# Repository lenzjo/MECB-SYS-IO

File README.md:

# TLC SYS-IO for MECB

This board consists of the following:

- SCC2691 ACIA

- WDC6522N

- RTC72421 - with battery backup

- ATTINY261A-P -for PS/2 Keyboard

I have brought out all available outputs along the top of the PCB, however, the PS/2 clock and data signals are also on the connector (pins C11 and A12 repectively) as are TxD (A16), RxD (A17), RTS (C16) and CTS (C19).

Use at your own risk as I have not had time yet to fully test the PCB. 

Also, the battery holder is an SMD part. It's easy enough to attach, I used a heat gun from underneath the pcb.

UPDATES

1.3 - Fixed Reset line on SCC2691, updated battery holder.

1.4 - Fixed KYBD clk line.

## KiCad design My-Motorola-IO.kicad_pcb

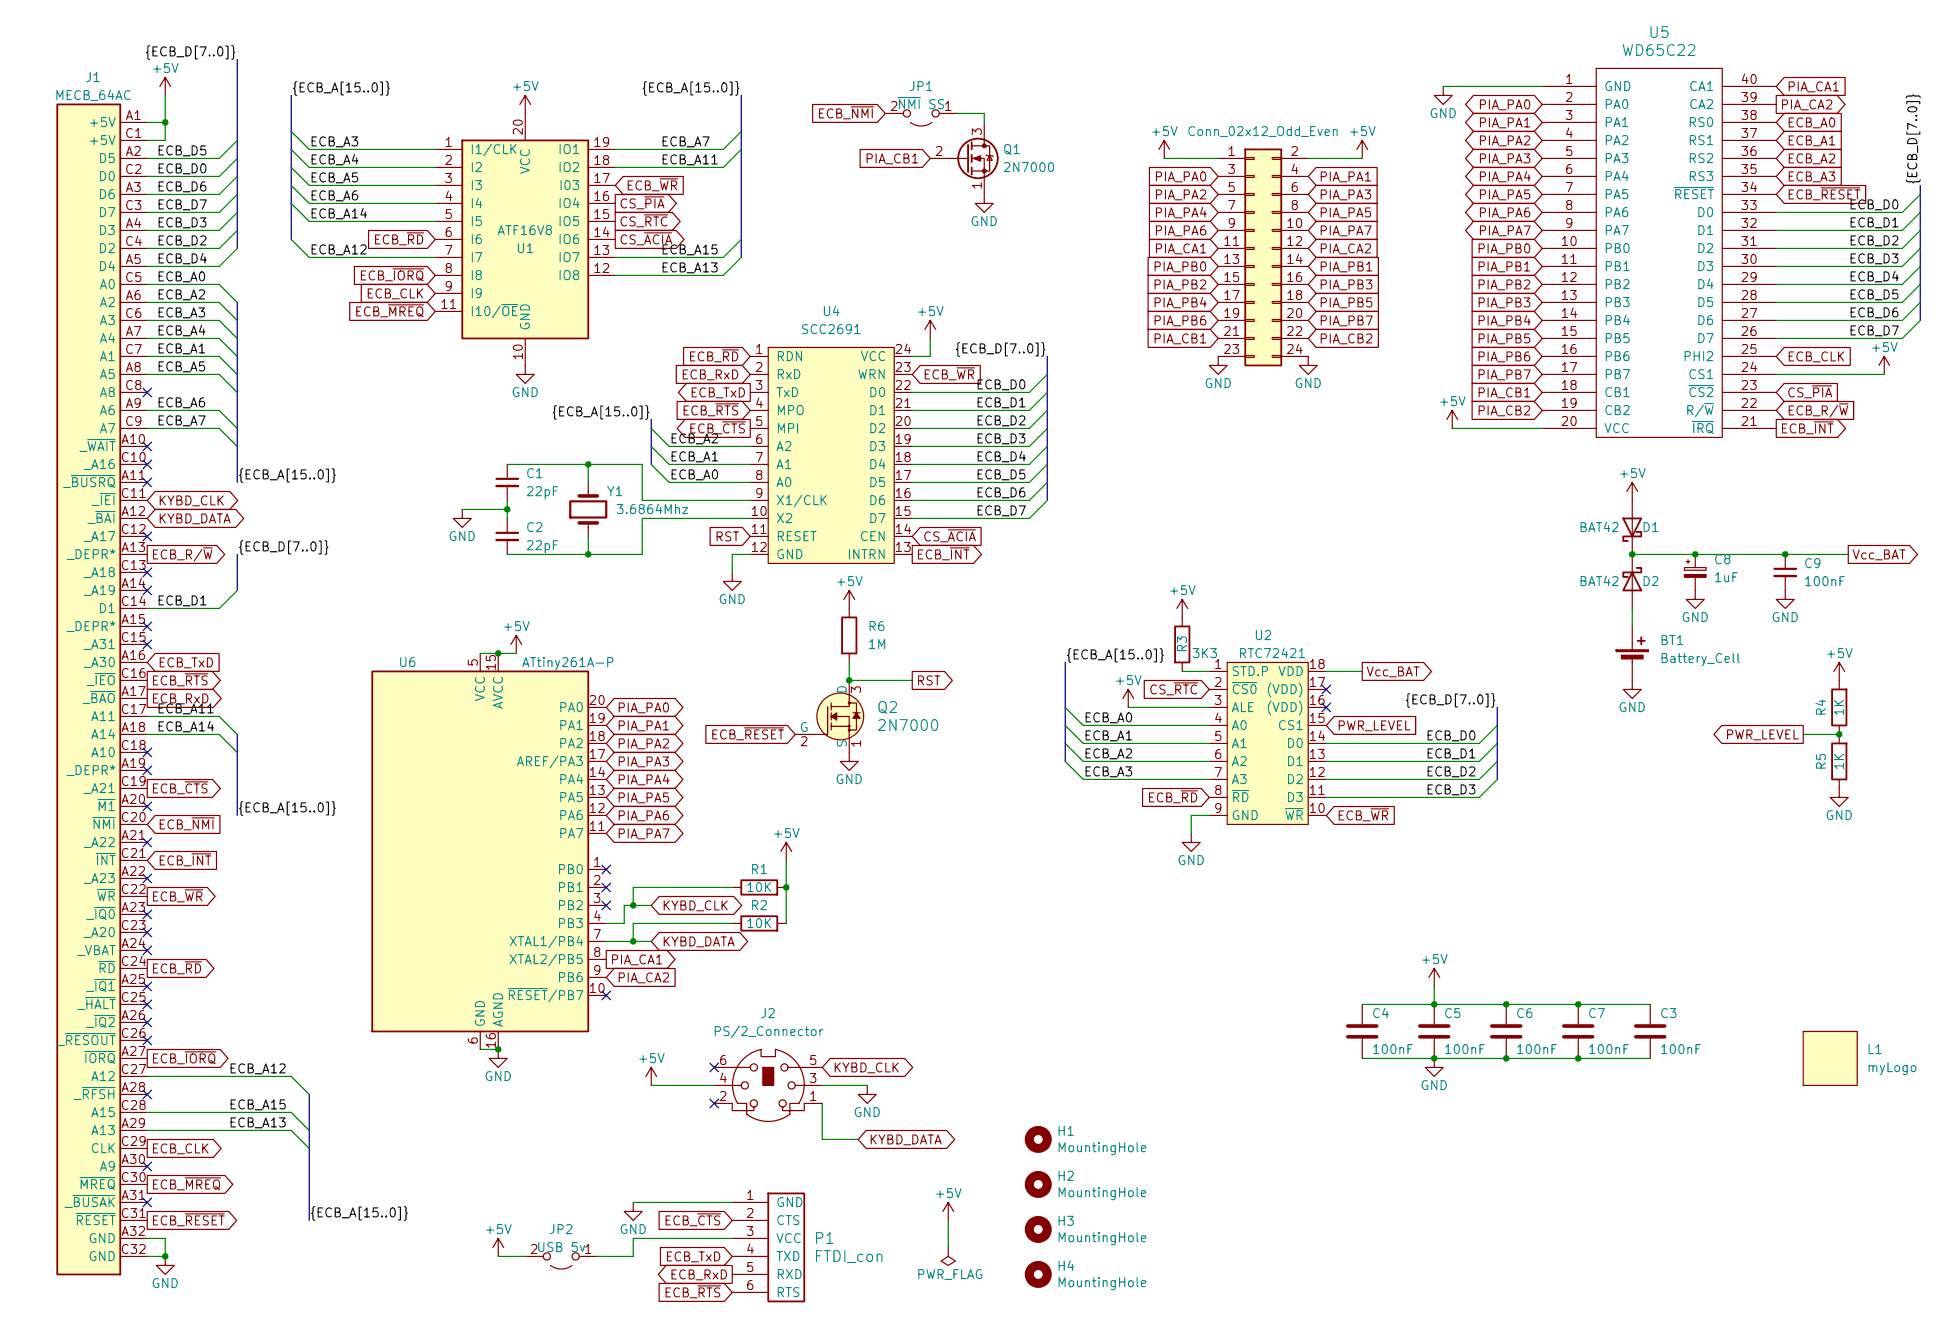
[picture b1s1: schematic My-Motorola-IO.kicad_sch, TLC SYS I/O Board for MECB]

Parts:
BT1: Battery_Cell; SMD CR2032
C1, C2: 22pF; C_Disc_D4.7mm_W2.5mm_P5.00mm
C3, C4, C5, C6, C7: 100nF; C_Disc_D4.7mm_W2.5mm_P5.00mm
C8: 1uF; CP_Radial_D5.0mm_P2.50mm
C9: 100nF; C_Disc_D5.1mm_W3.2mm_P5.00mm
D1, D2: BAT42; D_DO-35_SOD27_P7.62mm_Horizontal
H1, H2, H3, H4: MountingHole; MountingHole_3.2mm_M3
J1: MECB_64AC; DIN41612_C_2x32_C64AC_Male_Horizontal_THT
J2: PS/2_Connector; PS2_mini_DIN
J6: Conn_02x12_Odd_Even; PinHeader_2x12_P2.54mm_Horizontal
JP1: ~{NMI} SS; PinHeader_1x02_P2.54mm_Vertical
JP2: USB 5v; SolderJumper-2_P1.3mm_Open_RoundedPad1.0x1.5mm
L1: myLogo; Logo11x13
P1: FTDI_con; PinHeader_1x06_P2.54mm_Horizontal
Q1: 2N7000; TO-92_Inline
Q2: 2N7000; TO-92_Inline; MPN 2N7000; Digi-Key_PN 2N7000FS-ND
R1, R2: 10K; R_Axial_DIN0207_L6.3mm_D2.5mm_P10.16mm_Horizontal
R3: 3K3; R_Axial_DIN0207_L6.3mm_D2.5mm_P10.16mm_Horizontal
R4, R5: 1K; R_Axial_DIN0207_L6.3mm_D2.5mm_P10.16mm_Horizontal
R6: 1M; R_Axial_DIN0207_L6.3mm_D2.5mm_P10.16mm_Horizontal
U1: ATF16V8; DIP-20_W7.62mm_Socket_LongPads
U2: RTC72421; DIP-18_W7.62mm_LongPads
U4: SCC2691; DIP-24_W7.62mm_LongPads
U5: WD65C22; DIP-40_W15.24mm_LongPads
U6: ATtiny261A-P; DIP-20_W7.62mm_LongPads
Y1: 3.6864Mhz; Crystal_HC49-U_Vertical

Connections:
+5V: C3.1, C4.1, C5.1, C6.1, C7.1, D1.2 (A), J1.A1 (+5V), J1.C1 (+5V), J2.4, J6.1, J6.2, JP2.2 (B), R1.2, R2.2, R3.1, R4.2, R6.1, U1.20 (VCC), U2.3 (ALE), U4.24 (VCC), U5.20 (VCC), U5.24 (CS1), U6.5 (VCC), U6.15 (AVCC)
/ECB_A4: J1.A7 (A4), U1.2 (I2)
/ECB_A5: J1.A8 (A5), U1.3 (I3)
/ECB_A6: J1.A9 (A6), U1.4 (I4)
/ECB_A7: J1.C9 (A7), U1.19 (IO1)
/ECB_A11: J1.C17 (A11), U1.18 (IO2)
/ECB_A12: J1.C27 (A12), U1.7 (I7)
/ECB_A13: J1.A29 (A13), U1.12 (IO8)
/ECB_A14: J1.A18 (A14), U1.5 (I5)
/ECB_A15: J1.C28 (A15), U1.13 (IO7)
/ECB_D0: J1.C2 (D0), U2.14 (D0), U4.22 (D0), U5.33 (D0)
/ECB_D1: J1.C14 (D1), U2.13 (D1), U4.21 (D1), U5.32 (D1)
/ECB_D2: J1.C4 (D2), U2.12 (D2), U4.20 (D2), U5.31 (D2)
/ECB_D3: J1.A4 (D3), U2.11 (D3), U4.19 (D3), U5.30 (D3)
/ECB_D4: J1.A5 (D4), U4.18 (D4), U5.29 (D4)
/ECB_D5: J1.A2 (D5), U4.17 (D5), U5.28 (D5)
/ECB_D6: J1.A3 (D6), U4.16 (D6), U5.27 (D6)
/ECB_D7: J1.C3 (D7), U4.15 (D7), U5.26 (D7)
CS_~ACIA: U1.14 (IO6), U4.14 (CEN)
CS_~PIA: U1.16 (IO4), U5.23 (~CS2)
CS_~RTC: U1.15 (IO5), U2.2 (~CS0)
ECB_A0: J1.C5 (A0), U2.4 (A0), U4.8 (A0), U5.38 (RS0)
ECB_A1: J1.C7 (A1), U2.5 (A1), U4.7 (A1), U5.37 (RS1)
ECB_A2: J1.A6 (A2), U2.6 (A2), U4.6 (A2), U5.36 (RS2)
ECB_A3: J1.C6 (A3), U1.1 (I1/CLK), U2.7 (A3), U5.35 (RS3)
ECB_CLK: J1.C29 (CLK), U1.9 (I9), U5.25 (PHI2)
ECB_RxD: J1.A17 (_~BAO), P1.5 (RXD), U4.2 (RxD)
ECB_R/~W: J1.A13 (_DEPR*), U5.22 (R/~W)
ECB_TxD: J1.A16 (_A30), P1.4 (TXD), U4.3 (TxD)
ECB_~CTS: J1.C19 (_A21), P1.2 (CTS), U4.5 (MPI)
ECB_~INT: J1.C21 (~INT), U4.13 (INTRN), U5.21 (~IRQ)
ECB_~IORQ: J1.A27 (~IORQ), U1.8 (I8)
ECB_~MREQ: J1.C30 (~MREQ), U1.11 (I10/~OE)
ECB_~NMI: J1.C20 (~NMI), JP1.2 (B)
ECB_~RD: J1.C24 (~RD), U1.6 (I6), U2.8 (~RD), U4.1 (RDN)
ECB_~RESET: J1.C31 (~RESET), Q2.2 (G), U5.34 (~RESET)
ECB_~RTS: J1.C16 (_~IEO), P1.6 (RTS), U4.4 (MPO)
ECB_~WR: J1.C22 (~WR), U1.17 (I03), U2.10 (~WR), U4.23 (WRN)
GND: BT1.2 (-), C1.2, C2.1, C3.2, C4.2, C5.2, C6.2, C7.2, C8.2, C9.2, J1.A32 (GND), J1.C32 (GND), J2.3, J6.23, J6.24, P1.1 (GND), Q1.1 (S), Q2.1 (S), R5.1, U1.10 (GND), U2.9 (GND), U4.12 (GND), U5.1 (GND), U6.6 (GND), U6.16 (AGND)
KYBD_CLK: J1.C11 (_~IEI), J2.5, R1.1, U6.4 (PB3)
KYBD_DATA: J1.A12 (_~BAI), J2.1, R2.1, U6.7 (XTAL1/PB4)
unnamed: BT1.1 (+), D2.2 (A)
unnamed: JP1.1 (A), Q1.3 (D)
unnamed: JP2.1 (A), P1.3 (VCC)
unnamed: R3.2, U2.1 (STD.P)
unnamed: C1.1, U4.9 (X1/CLK), Y1.2
unnamed: C2.2, U4.10 (X2), Y1.1
PIA_CA1: J6.11, U5.40 (CA1), U6.8 (XTAL2/PB5)
PIA_CA2: J6.12, U5.39 (CA2), U6.9 (PB6)
PIA_CB1: J6.21, Q1.2 (G), U5.18 (CB1)
PIA_CB2: J6.22, U5.19 (CB2)
PIA_PA0: J6.3, U5.2 (PA0), U6.20 (PA0)
PIA_PA1: J6.4, U5.3 (PA1), U6.19 (PA1)
PIA_PA2: J6.5, U5.4 (PA2), U6.18 (PA2)
PIA_PA3: J6.6, U5.5 (PA3), U6.17 (AREF/PA3)
PIA_PA4: J6.7, U5.6 (PA4), U6.14 (PA4)
PIA_PA5: J6.8, U5.7 (PA5), U6.13 (PA5)
PIA_PA6: J6.9, U5.8 (PA6), U6.12 (PA6)
PIA_PA7: J6.10, U5.9 (PA7), U6.11 (PA7)
PIA_PB0: J6.13, U5.10 (PB0)
PIA_PB1: J6.14, U5.11 (PB1)
PIA_PB2: J6.15, U5.12 (PB2)
PIA_PB3: J6.16, U5.13 (PB3)
PIA_PB4: J6.17, U5.14 (PB4)
PIA_PB5: J6.18, U5.15 (PB5)
PIA_PB6: J6.19, U5.16 (PB6)
PIA_PB7: J6.20, U5.17 (PB7)
PWR_LEVEL: R4.1, R5.2, U2.15 (CS1)
RST: Q2.3 (D), R6.2, U4.11 (RESET)
Vcc_BAT: C8.1, C9.1, D1.1 (K), D2.1 (K), U2.18 (VDD)

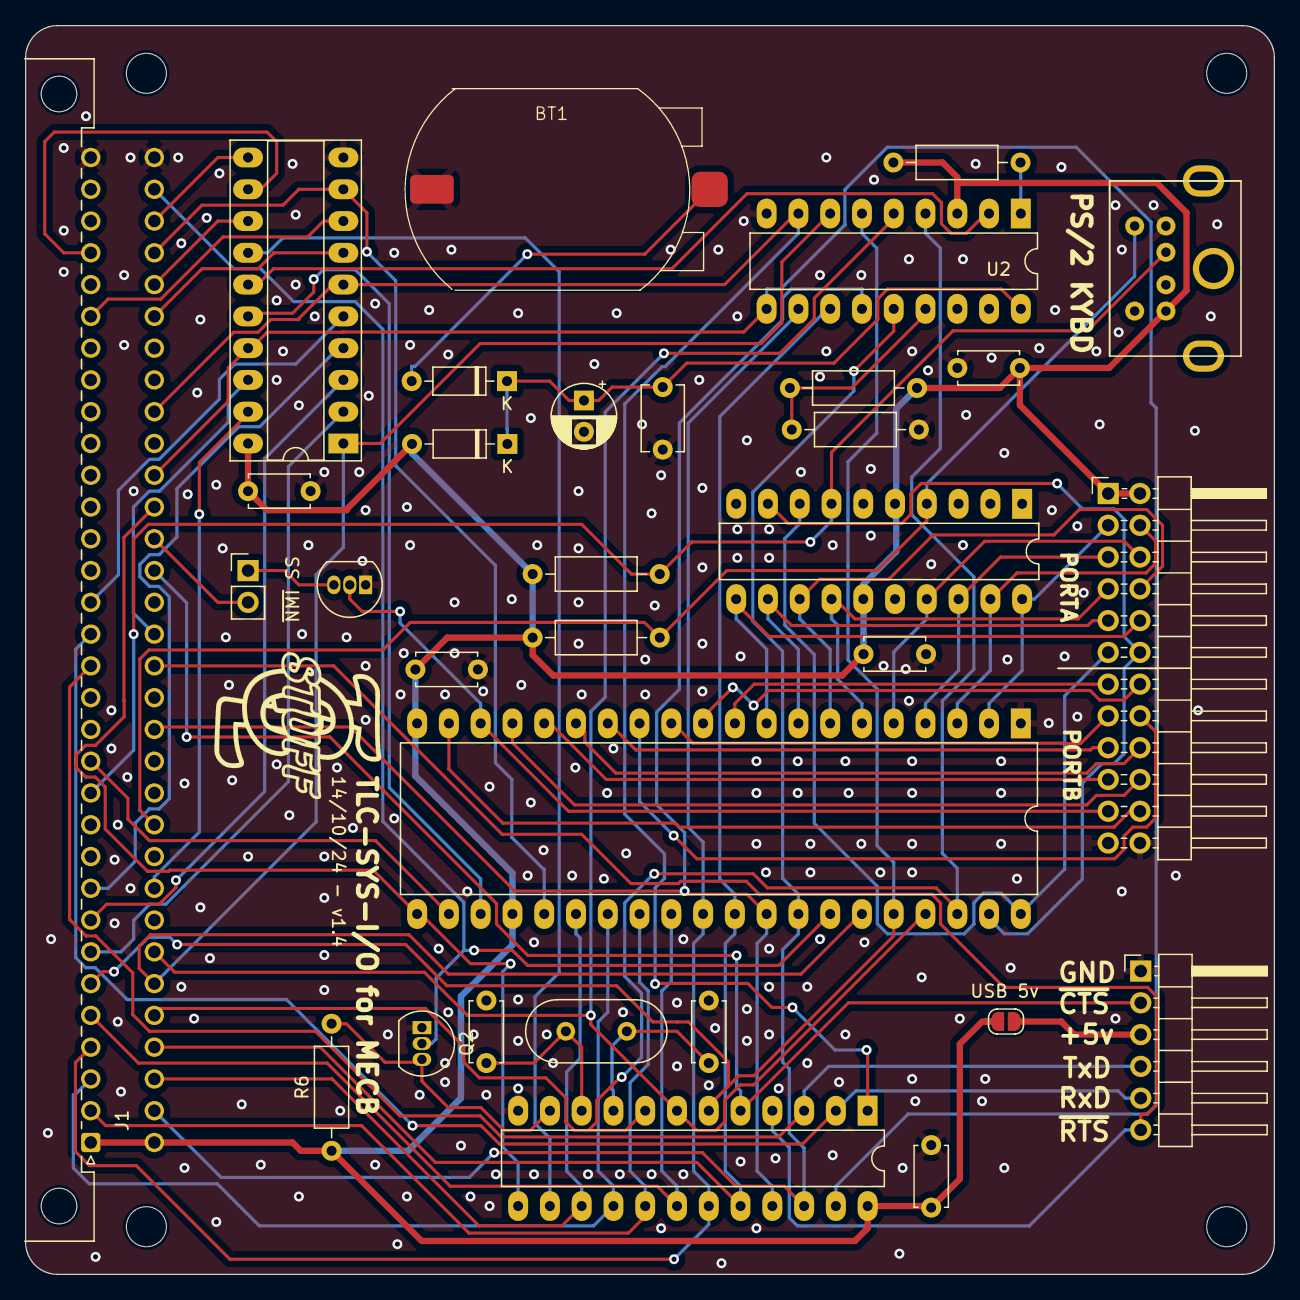
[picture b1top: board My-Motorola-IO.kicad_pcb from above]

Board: 2 copper layers, 99.8 x 99.8 mm, 37 parts (0 on the bottom side), 70 nets.

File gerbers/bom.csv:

Designator,Footprint,Quantity,Value,LCSC Part #
BT1,SMD CR2032,1,Battery_Cell,
"C1, C2",C_Disc_D4.7mm_W2.5mm_P5.00mm,2,22pF,
"C3, C4, C5, C6, C7",C_Disc_D4.7mm_W2.5mm_P5.00mm,5,100nF,
C8,CP_Radial_D5.0mm_P2.50mm,1,1uF,
C9,C_Disc_D5.1mm_W3.2mm_P5.00mm,1,100nF,
"D1, D2",D_DO-35_SOD27_P7.62mm_Horizontal,2,BAT42,
"H1, H2, H3, H4",MountingHole_3.2mm_M3,4,MountingHole,
J1,DIN41612_C_2x32_C64AC_Male_Horizontal_THT,1,MECB_64AC,
J2,PS2_mini_DIN,1,PS/2_Connector,
J6,PinHeader_2x12_P2.54mm_Horizontal,1,Conn_02x12_Odd_Even,
JP1,PinHeader_1x02_P2.54mm_Vertical,1,~{NMI} SS,
JP2,SolderJumper-2_P1.3mm_Open_RoundedPad1.0x1.5mm,1,USB 5v,
L1,Logo11x13,1,myLogo,
P1,PinHeader_1x06_P2.54mm_Horizontal,1,FTDI_con,
Q1,TO-92_Inline,1,2N7000,
Q2,TO-92_Inline,1,2N7000,2N7000
"R1, R2",R_Axial_DIN0207_L6.3mm_D2.5mm_P10.16mm_Horizontal,2,10K,
R3,R_Axial_DIN0207_L6.3mm_D2.5mm_P10.16mm_Horizontal,1,3K3,
"R4, R5",R_Axial_DIN0207_L6.3mm_D2.5mm_P10.16mm_Horizontal,2,1K,
R6,R_Axial_DIN0207_L6.3mm_D2.5mm_P10.16mm_Horizontal,1,1M,
U1,DIP-20_W7.62mm_Socket_LongPads,1,ATF16V8,
U2,DIP-18_W7.62mm_LongPads,1,RTC72421,
U4,DIP-24_W7.62mm_LongPads,1,SCC2691,
U5,DIP-40_W15.24mm_LongPads,1,WD65C22,
U6,DIP-20_W7.62mm_LongPads,1,ATtiny261A-P,
Y1,Crystal_HC49-U_Vertical,1,3.6864Mhz,

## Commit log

2024-07-21 readme update
2024-09-10 updated SCC2691 reset line and battery holder
2024-10-13 KEYBD clk fixed, added missing pwr trace
